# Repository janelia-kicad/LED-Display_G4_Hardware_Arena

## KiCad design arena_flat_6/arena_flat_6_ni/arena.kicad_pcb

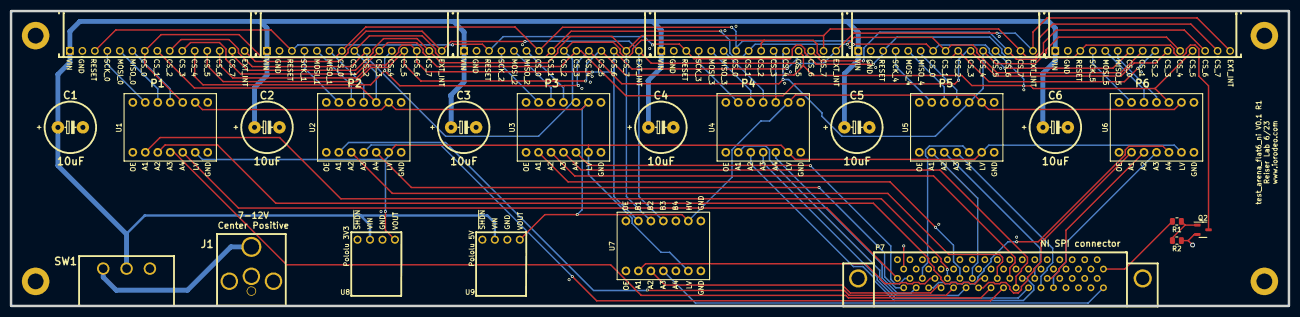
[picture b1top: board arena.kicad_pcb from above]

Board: 4 copper layers, 260.0 x 60.0 mm, 31 parts (0 on the bottom side), 62 nets.

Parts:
C1, C2, C3, C4, C5, C6: 10uF; Capacitor_Polarized
H1, H2, H3, H4: MountingHole_Pad; MountingHole_3.2mm_M3_DIN965_Pad
J1: Barrel_Jack; DCJACK_2PIN_HIGHCURRENT
P1, P2, P3, P4, P5, P6: CONN15; HEADER_TOP
P7: CONN_34X2; TE_CONN_DSUB_RA_68
Q2: MOSFET_NCHAN; SOT-23-3
R1: 200; R_0805_2012Metric
R2: 20k; R_0805_2012Metric
SW1: SW_SPDT; slide_switch
U1, U2, U3, U4, U5, U6, U7: VAL**; SPARKFUN_TXB0104
U8, U9: POLOLU_D24V6Fx; D24V6Fx

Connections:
/3V3: U1.6 (LV), U2.6 (LV), U3.6 (LV), U4.6 (LV), U5.6 (LV), U6.6 (LV), U7.6 (LV), U8.4 (VOUT)
/5V: U1.9 (HV), U2.9 (HV), U3.9 (HV), U4.9 (HV), U5.9 (HV), U6.9 (HV), U7.9 (HV), U9.4 (VOUT)
/CS_0_3V3: P7.35, U1.5 (A4)
/CS_0_5V: P1.7, P2.7, P3.7, P4.7, P5.7, P6.7, U1.10 (B4)
/CS_1_3V3: P7.36, U2.5 (A4)
/CS_1_5V: P1.8, P2.8, P3.8, P4.8, P5.8, P6.8, U2.10 (B4)
/CS_2_3V3: P7.37, U3.5 (A4)
/CS_2_5V: P1.9, P2.9, P3.9, P4.9, P5.9, P6.9, U3.10 (B4)
/CS_3_3V3: P7.38, U4.5 (A4)
/CS_3_5V: P1.10, P2.10, P3.10, P4.10, P5.10, P6.10, U4.10 (B4)
/CS_4_3V3: P7.39, U5.5 (A4)
/CS_4_5V: P1.11, P2.11, P3.11, P4.11, P5.11, P6.11, U5.10 (B4)
/CS_5_3V3: P7.40, U6.5 (A4)
/CS_5_5V: P1.12, P2.12, P3.12, P4.12, P5.12, P6.12, U6.10 (B4)
/CS_6_3V3: P7.41, U7.2 (A1)
/CS_6_5V: P1.13, P2.13, P3.13, P4.13, P5.13, P6.13, U7.13 (B1)
/CS_7_3V3: P7.42, U7.3 (A2)
/CS_7_5V: P1.14, P2.14, P3.14, P4.14, P5.14, P6.14, U7.12 (B2)
/EXT_INT_3V3: P7.68, U7.4 (A3)
/EXT_INT_5V: P1.15, P2.15, P3.15, P4.15, P5.15, P6.15, U7.11 (B3)
/MISO_0_3V3: P7.50, U1.4 (A3)
/MISO_0_5V: P1.6, U1.11 (B3)
/MISO_1_3V3: P7.52, U2.4 (A3)
/MISO_1_5V: P2.6, U2.11 (B3)
/MISO_2_3V3: P7.54, U3.4 (A3)
/MISO_2_5V: P3.6, U3.11 (B3)
/MISO_3_3V3: P7.56, U4.4 (A3)
/MISO_3_5V: P4.6, U4.11 (B3)
/MISO_4_3V3: P7.58, U5.4 (A3)
/MISO_4_5V: P5.6, U5.11 (B3)
/MISO_5_3V3: P7.60, U6.4 (A3)
/MISO_5_5V: P6.6, U6.11 (B3)
/MOSI_0_3V3: P7.49, U1.3 (A2)
/MOSI_0_5V: P1.5, U1.12 (B2)
/MOSI_1_3V3: P7.51, U2.3 (A2)
/MOSI_1_5V: P2.5, U2.12 (B2)
/MOSI_2_3V3: P7.53, U3.3 (A2)
/MOSI_2_5V: P3.5, U3.12 (B2)
/MOSI_3_3V3: P7.55, U4.3 (A2)
/MOSI_3_5V: P4.5, U4.12 (B2)
/MOSI_4_3V3: P7.57, U5.3 (A2)
/MOSI_4_5V: P5.5, U5.12 (B2)
/MOSI_5_3V3: P7.59, U6.3 (A2)
/MOSI_5_5V: P6.5, U6.12 (B2)
/RESET: P7.34, R1.2
/RESET_PAN: P1.3, P2.3, P3.3, P4.3, P5.3, P6.3, Q2.3 (D)
/SCK_0_3V3: P7.43, U1.2 (A1)
/SCK_0_5V: P1.4, U1.13 (B1)
/SCK_1_3V3: P7.44, U2.2 (A1)
/SCK_1_5V: P2.4, U2.13 (B1)
/SCK_2_3V3: P7.45, U3.2 (A1)
/SCK_2_5V: P3.4, U3.13 (B1)
/SCK_3_3V3: P7.46, U4.2 (A1)
/SCK_3_5V: P4.4, U4.13 (B1)
/SCK_4_3V3: P7.47, U5.2 (A1)
/SCK_4_5V: P5.4, U5.13 (B1)
/SCK_5_3V3: P7.48, U6.2 (A1)
/SCK_5_5V: P6.4, U6.13 (B1)
/VIN: C1.1, C2.1, C3.1, C4.1, C5.1, C6.1, P1.1, P2.1, P3.1, P4.1, P5.1, P6.1, SW1.2 (B), U8.2 (VIN), U9.2 (VIN)
/VIN_SW: J1.1, SW1.1 (A)
GND: C1.2, C2.2, C3.2, C4.2, C5.2, C6.2, H1.1, H2.1, H3.1, H4.1, J1.2, P1.2, P2.2, P3.2, P4.2, P5.2, P6.2, P7.1, P7.2, P7.3, P7.69, Q2.2 (S), R2.1, SW1.3 (C), U1.7 (GND), U1.8 (GND), U2.7 (GND), U2.8 (GND), U3.7 (GND), U3.8 (GND), U4.7 (GND), U4.8 (GND), U5.7 (GND), U5.8 (GND), U6.7 (GND), U6.8 (GND), U7.7 (GND), U7.8 (GND), U8.3 (GND), U9.3 (GND)
unnamed: Q2.1 (G), R1.1, R2.2

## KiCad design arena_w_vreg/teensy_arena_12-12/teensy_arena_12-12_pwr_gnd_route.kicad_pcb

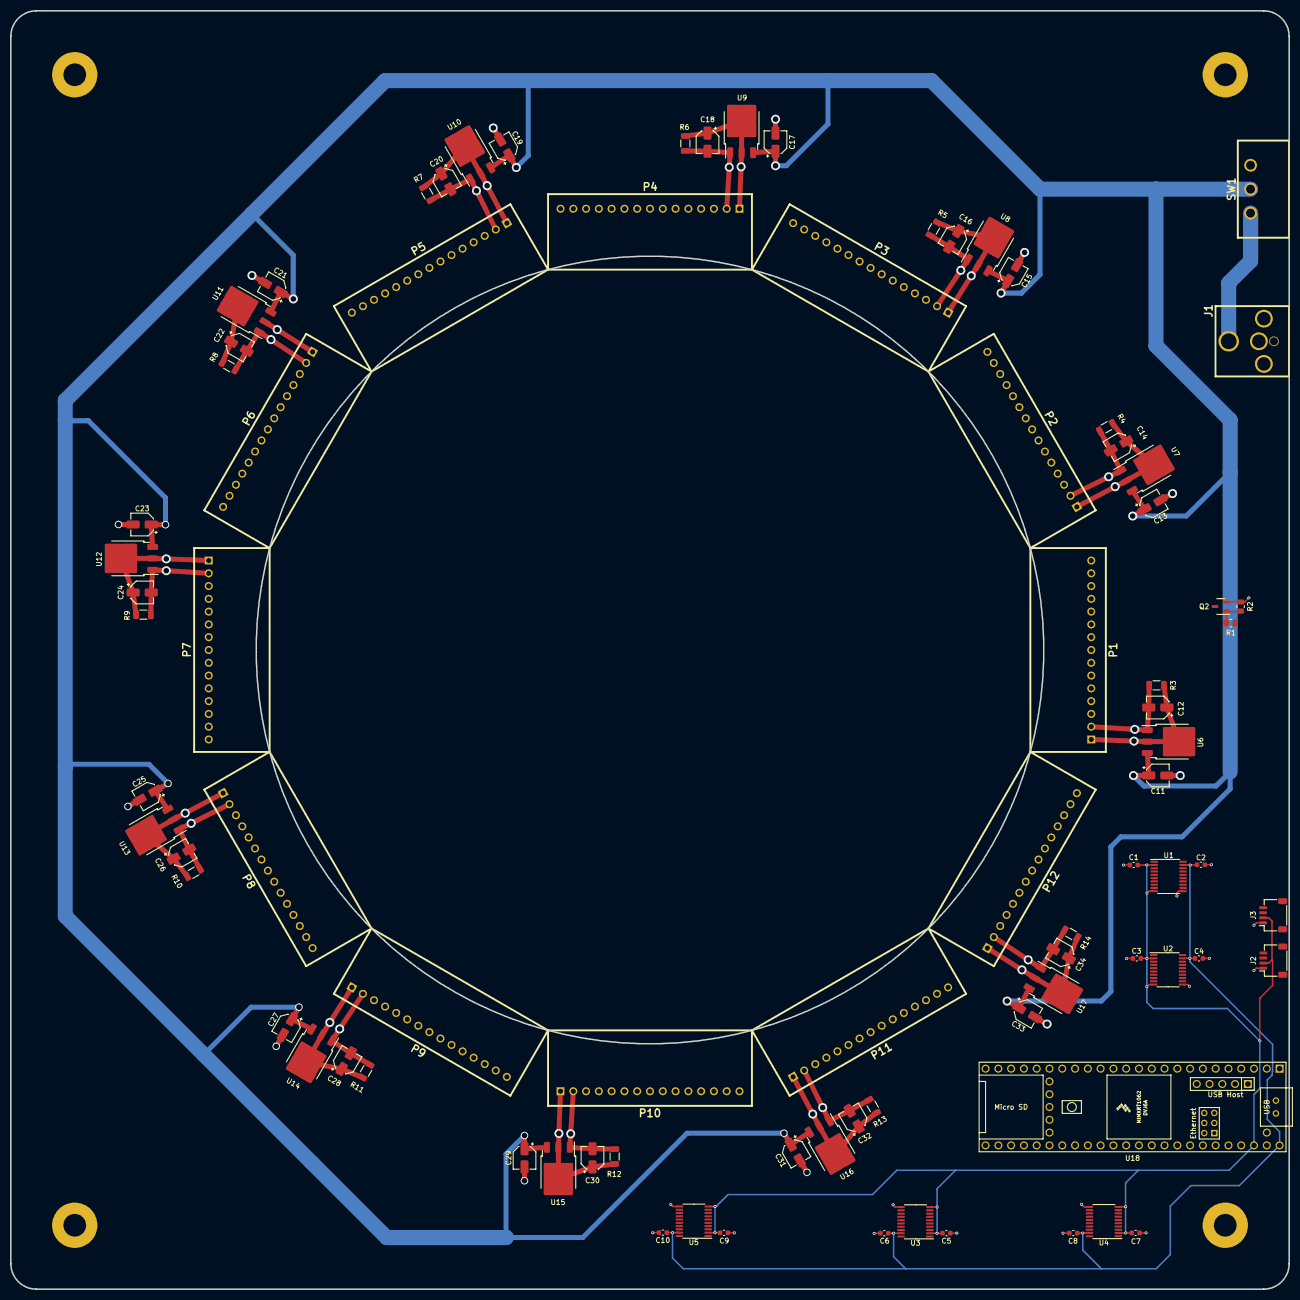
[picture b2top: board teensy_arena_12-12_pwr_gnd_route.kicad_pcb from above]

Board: 4 copper layers, 254.0 x 254.0 mm, 87 parts (0 on the bottom side), 98 nets.

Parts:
C1, C2, C3, C4, C5, C6, C7, C8, C9, C10: 0.1uF; C_0603_1608Metric
C11, C13, C15, C17, C21, C23, C25, C27, C29, C31, C33: 10uF; CP_Elec_4x5.4
C12, C14, C16, C18, C20, C22, C24, C26, C28, C30, C32, C34: 22uF; CP_Elec_4x5.4
C19: 10F; CP_Elec_4x5.4
H1, H2, H3, H4: MountingHole_Pad; MountingHole_4.5mm_Pad
J1: Barrel_Jack; DCJACK_2PIN_HIGHCURRENT
J2, J3: Conn_01x04; JST_SH_SM04B-SRSS-TB_1x04-1MP_P1.00mm_Horizontal
P1, P2, P3, P4, P5, P6, P7, P8, P9, P10, P11, P12: CONN15; HEADER_TOP
Q2: MOSFET_NCHAN; SOT-23-3
R1: 200; R_0805_2012Metric
R2: 20k; R_0805_2012Metric
R3, R4, R5, R6, R7, R8, R9, R10, R11, R12, R13, R14: 300; C_1206_3216Metric
SW1: SW_SPDT; slide_switch
U1, U2, U3, U4, U5: TXB0108PW; TSSOP-20_4.4x6.5mm_P0.65mm
U6, U7, U8, U9, U10, U11, U12, U13, U14, U15, U16, U17: AZ1084-5.0; TO-252-3_TabPin2
U18: Teensy4.1; Teensy41

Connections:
+3.3V: C1.1, C3.1, C5.1, C7.1, C9.1, J2.2, J3.2, U1.2 (VCCA), U1.10 (OE), U2.2 (VCCA), U2.10 (OE), U3.2 (VCCA), U3.10 (OE), U4.2 (VCCA), U4.10 (OE), U5.2 (VCCA), U5.10 (OE), U18.15 (3V3), U18.46 (3V3)
+5V: C2.1, C4.1, C6.1, C8.1, C10.1, U1.19 (VCCB), U2.19 (VCCB), U3.19 (VCCB), U4.19 (VCCB), U5.19 (VCCB), U18.48 (VIN), U18.49 (VUSB)
/Level Shifters/PAN3V.CS_00: U2.1 (A1), U18.2 (0_RX1_CRX2_CS1)
/Level Shifters/PAN3V.CS_01: U2.3 (A2), U18.4 (2_OUT2)
/Level Shifters/PAN3V.CS_02: U2.4 (A3), U18.5 (3_LRCLK2)
/Level Shifters/PAN3V.CS_03: U2.5 (A4), U18.6 (4_BCLK2)
/Level Shifters/PAN3V.CS_04: U2.6 (A5), U18.7 (5_IN2)
/Level Shifters/PAN3V.CS_05: U2.7 (A6), U18.8 (6_OUT1D)
/Level Shifters/PAN3V.CS_06: U2.8 (A7), U18.9 (7_RX2_OUT1A)
/Level Shifters/PAN3V.CS_07: U2.9 (A8), U18.10 (8_TX2_IN1)
/Level Shifters/PAN3V.CS_08: U3.1 (A1), U18.11 (9_OUT1C)
/Level Shifters/PAN3V.CS_09: U3.3 (A2), U18.12 (10_CS_MQSR)
/Level Shifters/PAN3V.CS_10: U3.4 (A3), U18.16 (24_A10_TX6_SCL2)
/Level Shifters/PAN3V.CS_11: U3.5 (A4), U18.17 (25_A11_RX6_SDA2)
/Level Shifters/PAN3V.CS_12: U3.6 (A5), U18.20 (28_RX7)
/Level Shifters/PAN3V.CS_13: U3.7 (A6), U18.21 (29_TX7)
/Level Shifters/PAN3V.CS_14: U3.8 (A7), U18.22 (30_CRX3)
/Level Shifters/PAN3V.CS_15: U3.9 (A8), U18.23 (31_CTX3)
/Level Shifters/PAN3V.CS_16: U4.1 (A1), U18.24 (32_OUT1B)
/Level Shifters/PAN3V.CS_17: U4.3 (A2), U18.45 (23_A9_CRX1_MCLK1)
/Level Shifters/PAN3V.CS_18: U4.4 (A3), U18.44 (22_A8_CTX1)
/Level Shifters/PAN3V.CS_19: U4.5 (A4), U18.43 (21_A7_RX5_BCLK1)
/Level Shifters/PAN3V.CS_20: U4.6 (A5), U18.42 (20_A6_TX5_LRCLK1)
/Level Shifters/PAN3V.CS_21: U4.7 (A6), U18.39 (17_A3_TX4_SDA1)
/Level Shifters/PAN3V.CS_22: U4.8 (A7), U18.38 (16_A2_RX4_SCL1)
/Level Shifters/PAN3V.CS_23: U4.9 (A8), U18.33 (41_A17)
/Level Shifters/PAN3V.CS_24: U5.1 (A1), U18.32 (40_A16)
/Level Shifters/PAN3V.CS_25: U5.3 (A2), U18.31 (39_MISO1_OUT1A)
/Level Shifters/PAN3V.CS_26: U5.4 (A3), U18.30 (38_CS1_IN1)
/Level Shifters/PAN3V.CS_27: U5.5 (A4), U18.29 (37_CS)
/Level Shifters/PAN3V.CS_28: U5.6 (A5), U18.28 (36_CS)
/Level Shifters/PAN3V.CS_29: U5.7 (A6), U18.27 (35_TX8)
/Level Shifters/PAN3V.EXT_INT: U5.9 (A8), U18.25 (33_MCLK2)
/Level Shifters/PAN3V.MISO_0: U1.5 (A4), U18.14 (12_MISO_MQSL)
/Level Shifters/PAN3V.MISO_1: U1.9 (A8), U18.3 (1_TX1_CTX2_MISO1)
/Level Shifters/PAN3V.MOSI_0: U1.4 (A3), U18.13 (11_MOSI_CTX1)
/Level Shifters/PAN3V.MOSI_1: U1.8 (A7), U18.18 (26_A12_MOSI1)
/Level Shifters/PAN3V.RESET: U1.1 (A1), U18.26 (34_RX8)
/Level Shifters/PAN3V.SCK_0: U1.3 (A2), U18.35 (13_SCK_LED)
/Level Shifters/PAN3V.SCK_1: U1.7 (A6), U18.19 (27_A13_SCK1)
/Level Shifters/PAN5V.CS_00: P1.7, P7.7, U2.20 (B1)
/Level Shifters/PAN5V.CS_01: P1.8, P7.8, U2.18 (B2)
/Level Shifters/PAN5V.CS_02: P1.9, P7.9, U2.17 (B3)
/Level Shifters/PAN5V.CS_03: P1.10, P7.10, U2.16 (B4)
/Level Shifters/PAN5V.CS_04: P1.11, P7.11, U2.15 (B5)
/Level Shifters/PAN5V.CS_05: P2.7, P8.7, U2.14 (B6)
/Level Shifters/PAN5V.CS_06: P2.8, P2.9, P8.8, P8.9, U2.13 (B7)
/Level Shifters/PAN5V.CS_08: P2.10, P8.10, U3.20 (B1)
/Level Shifters/PAN5V.CS_09: P2.11, P8.11, U3.18 (B2)
/Level Shifters/PAN5V.CS_10: P3.7, P9.7, U3.17 (B3)
/Level Shifters/PAN5V.CS_11: P3.8, P9.8, U3.16 (B4)
/Level Shifters/PAN5V.CS_12: P3.9, P9.9, U3.15 (B5)
/Level Shifters/PAN5V.CS_13: P3.10, P9.10, U3.14 (B6)
/Level Shifters/PAN5V.CS_14: P3.11, P9.11, U3.13 (B7)
/Level Shifters/PAN5V.CS_15: P4.7, P10.7, U3.12 (B8)
/Level Shifters/PAN5V.CS_16: P4.8, P10.8, U4.20 (B1)
/Level Shifters/PAN5V.CS_17: P4.9, P10.9, U4.18 (B2)
/Level Shifters/PAN5V.CS_18: P4.10, P10.10, U4.17 (B3)
/Level Shifters/PAN5V.CS_19: P4.11, P10.11, U4.16 (B4)
/Level Shifters/PAN5V.CS_20: P5.7, P11.7, U4.15 (B5)
/Level Shifters/PAN5V.CS_21: P5.8, P11.8, U4.14 (B6)
/Level Shifters/PAN5V.CS_22: P5.9, P11.9, U4.13 (B7)
/Level Shifters/PAN5V.CS_23: P5.10, P11.10, U4.12 (B8)
/Level Shifters/PAN5V.CS_24: P5.11, P11.11, U5.20 (B1)
/Level Shifters/PAN5V.CS_25: P6.7, P12.7, U5.18 (B2)
/Level Shifters/PAN5V.CS_26: P6.8, P12.8, U5.17 (B3)
/Level Shifters/PAN5V.CS_27: P6.9, P12.9, U5.16 (B4)
/Level Shifters/PAN5V.CS_28: P6.10, P12.10, U5.15 (B5)
/Level Shifters/PAN5V.CS_29: P6.11, P12.11, U5.14 (B6)
/Level Shifters/PAN5V.EXT_INT: P1.15, P2.15, P3.15, P4.15, P5.15, P6.15, P7.15, P8.15, P9.15, P10.15, P11.15, P12.15, U5.12 (B8)
/Level Shifters/PAN5V.MISO_0: P1.6, P2.6, P3.6, P4.6, P5.6, P6.6, U1.16 (B4)
/Level Shifters/PAN5V.MISO_1: P7.6, P8.6, P9.6, P10.6, P11.6, P12.6, U1.12 (B8)
/Level Shifters/PAN5V.MOSI_0: P1.5, P2.5, P3.5, P4.5, P5.5, P6.5, U1.17 (B3)
/Level Shifters/PAN5V.MOSI_1: P7.5, P8.5, P9.5, P10.5, P11.5, P12.5, U1.13 (B7)
/Level Shifters/PAN5V.RESET: R1.2, U1.20 (B1)
/Level Shifters/PAN5V.SCK_0: P1.4, P2.4, P3.4, P4.4, P5.4, P6.4, U1.18 (B2)
/Level Shifters/PAN5V.SCK_1: P7.4, P8.4, P9.4, P10.4, P11.4, P12.4, U1.14 (B6)
/Panel Headers/POW.5V_HDR_1: C12.1, P1.1, R3.1, U6.2 (VO)
/Panel Headers/POW.5V_HDR_2: C14.1, P2.1, R4.1, U7.2 (VO)
/Panel Headers/POW.5V_HDR_3: C16.1, P3.1, R5.1, U8.2 (VO)
/Panel Headers/POW.5V_HDR_4: C18.1, P4.1, R6.1, U9.2 (VO)
/Panel Headers/POW.5V_HDR_5: C20.1, P5.1, R7.1, U10.2 (VO)
/Panel Headers/POW.5V_HDR_6: C22.1, P6.1, R8.1, U11.2 (VO)
/Panel Headers/POW.5V_HDR_7: C24.1, P7.1, R9.1, U12.2 (VO)
/Panel Headers/POW.5V_HDR_8: C26.1, P8.1, R10.1, U13.2 (VO)
/Panel Headers/POW.5V_HDR_9: C28.1, P9.1, R11.1, U14.2 (VO)
/Panel Headers/POW.5V_HDR_10: C30.1, P10.1, R12.1, U15.2 (VO)
/Panel Headers/POW.5V_HDR_11: C32.1, P11.1, R13.1, U16.2 (VO)
/Panel Headers/POW.5V_HDR_12: C34.1, P12.1, R14.1, U17.2 (VO)
/Panel Headers/RESET: P1.3, P2.3, P3.3, P4.3, P5.3, P6.3, P7.3, P8.3, P9.3, P10.3, P11.3, P12.3, Q2.3 (D)
/Teensy/A0: J3.3, U18.36 (14_A0_TX3_SPDIF_OUT)
/Teensy/A1: J3.4, U18.37 (15_A1_RX3_SPDIF_IN)
/Teensy/SCL: J2.4, U18.41 (19_A5_SCL)
/Teensy/SDA: J2.3, U18.40 (18_A4_SDA)
GND: C1.2, C2.2, C3.2, C4.2, C5.2, C6.2, C7.2, C8.2, C9.2, C10.2, C11.2, C12.2, C13.2, C14.2, C15.2, C16.2, C17.2, C18.2, C19.2, C20.2, C21.2, C22.2, C23.2, C24.2, C25.2, C26.2, C27.2, C28.2, C29.2, C30.2, C31.2, C32.2, C33.2, C34.2, H1.1, H2.1, H3.1, H4.1, J1.2, J2.1, J3.1, P1.2, P2.2, P3.2, P4.2, P5.2, P6.2, P7.2, P8.2, P9.2, P10.2, P11.2, P12.2, Q2.2 (S), R2.1, R3.2, R4.2, R5.2, R6.2, R7.2, R8.2, R9.2, R10.2, R11.2, R12.2, R13.2, R14.2, SW1.3 (C), U1.11 (GND), U2.11 (GND), U3.11 (GND), U4.11 (GND), U5.11 (GND), U6.1 (GND), U7.1 (GND), U8.1 (GND), U9.1 (GND), U10.1 (GND), U11.1 (GND), U12.1 (GND), U13.1 (GND), U14.1 (GND), U15.1 (GND), U16.1 (GND), U17.1 (GND), U18.1 (GND), U18.34 (GND), U18.47 (GND)
unnamed: Q2.1 (G), R1.1, R2.2
unnamed: J1.1, SW1.1 (A)
VCC: C11.1, C13.1, C15.1, C17.1, C19.1, C21.1, C23.1, C25.1, C27.1, C29.1, C31.1, C33.1, SW1.2 (B), U6.3 (VI), U7.3 (VI), U8.3 (VI), U9.3 (VI), U10.3 (VI), U11.3 (VI), U12.3 (VI), U13.3 (VI), U14.3 (VI), U15.3 (VI), U16.3 (VI), U17.3 (VI)

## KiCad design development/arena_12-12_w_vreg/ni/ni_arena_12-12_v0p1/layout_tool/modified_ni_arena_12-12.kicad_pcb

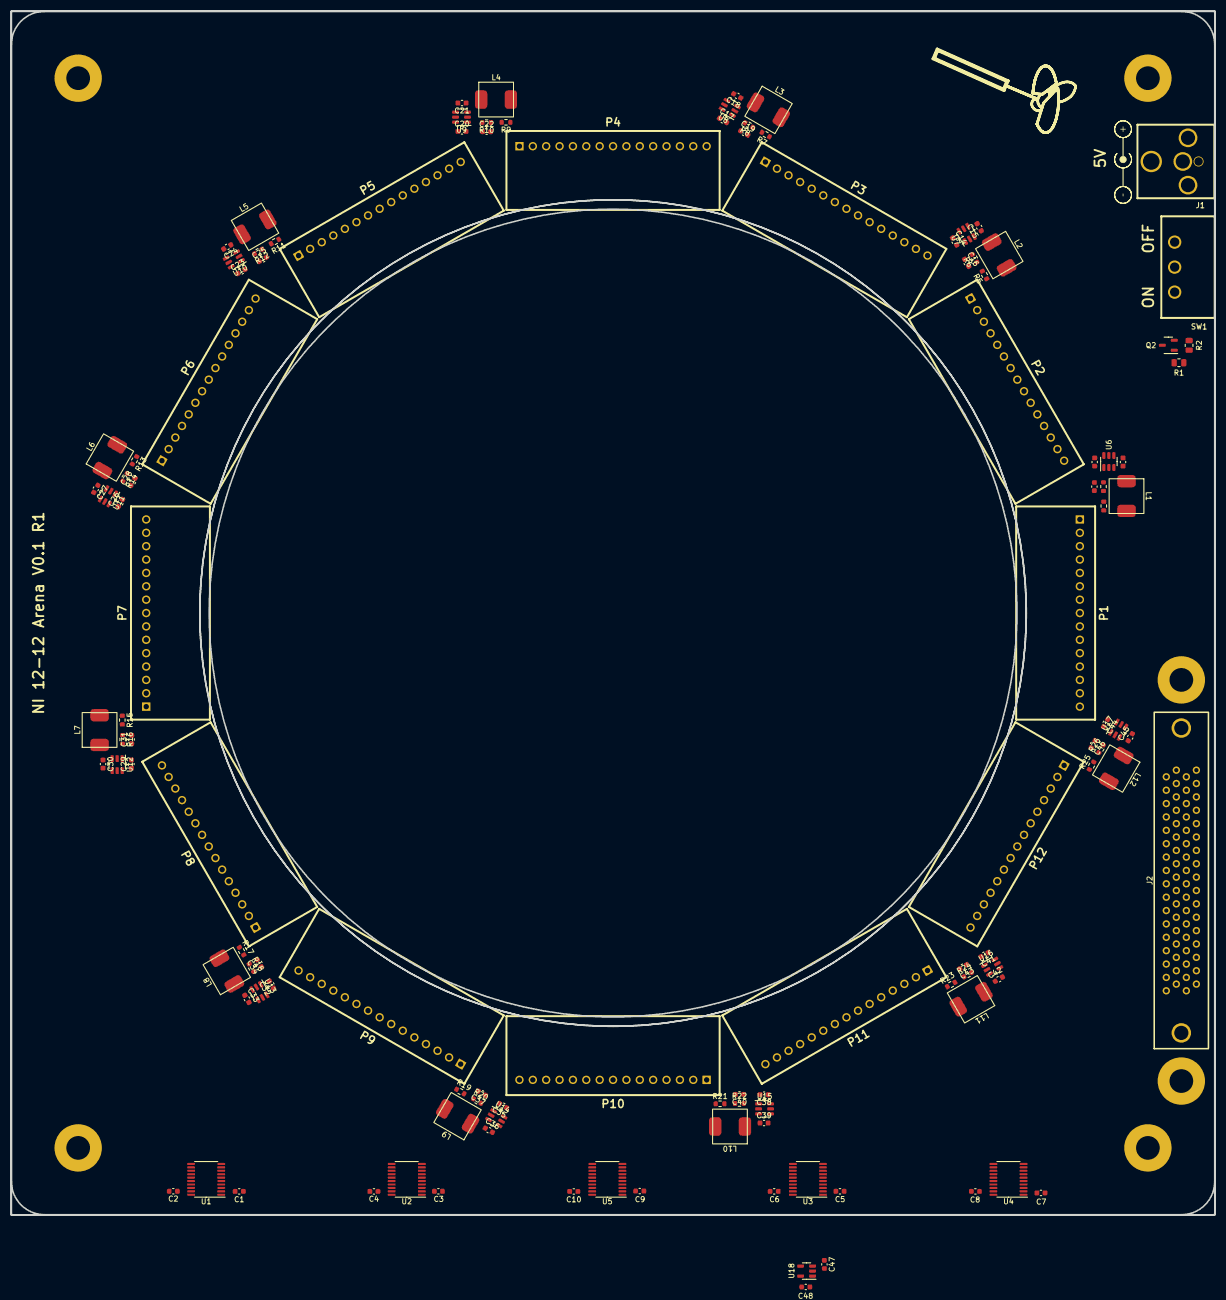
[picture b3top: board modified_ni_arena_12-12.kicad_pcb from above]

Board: 4 copper layers, 228.6 x 228.6 mm, 126 parts (0 on the bottom side), 134 nets, no tracks yet.

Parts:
C1, C2, C3, C4, C5, C6, C7, C8, C9, C10: 0.1uF; C_0603_1608Metric
C11, C15, C18, C21, C24, C27, C30, C33, C36, C39, C42, C45: 100nF; C_0603_1608Metric
C12, C14, C17, C20, C23, C26, C29, C32, C35, C38, C41, C44, C47, C48: 10uF; C_0603_1608Metric
C13, C16, C19, C22, C25, C28, C31, C34, C37, C40, C43, C46: 22uF; C_0603_1608Metric
H1, H2, H3, H4, H5, H6: MountingHole_Pad; MountingHole_4.5mm_Pad
J1: Barrel_Jack; DCJACK_2PIN_HIGHCURRENT
J2: NI_TE_68pos; TE_CONN_DSUB_VERT_68
L1, L2, L3, L4, L5, L6, L7, L8, L9, L10, L11, L12: 3.3uH; CYA0650_3P3UH
P1, P2, P3, P4, P5, P6, P7, P8, P9, P10, P11, P12: CONN15; HEADER_TOP
Q2: MOSFET_NCHAN; SOT-23-3
R1: 200; R_0805_2012Metric
R2: 20k; R_0805_2012Metric
R3, R5, R7, R9, R11, R13, R15, R17, R19, R21, R23, R25: 56.2k; R_0603_1608Metric
R4, R6, R8, R10, R12, R14, R16, R18, R20, R22, R24, R26: 10k; R_0603_1608Metric
SW1: SW_SPDT; slide_switch
U1, U2, U3, U4, U5: TXB0108PW; TSSOP-20_4.4x6.5mm_P0.65mm
U6, U7, U8, U9, U10, U11, U12, U13, U14, U15, U16, U17: TPS564201DDC; SOT-23-6
U18: AP2112K-3.3; SOT-23-5

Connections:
+3.3V: C1.1, C3.1, C5.1, C7.1, C9.1, C48.1, U1.2 (VCCA), U1.10 (OE), U2.2 (VCCA), U2.10 (OE), U3.2 (VCCA), U3.10 (OE), U4.2 (VCCA), U4.10 (OE), U5.2 (VCCA), U5.10 (OE), U18.5 (VOUT)
/Level Shifters/PAN3V.CS_00: J2.68, U1.1 (A1)
/Level Shifters/PAN3V.CS_01: J2.67, U1.3 (A2)
/Level Shifters/PAN3V.CS_02: J2.66, U1.4 (A3)
/Level Shifters/PAN3V.CS_03: J2.65, U1.5 (A4)
/Level Shifters/PAN3V.CS_04: J2.64, U1.6 (A5)
/Level Shifters/PAN3V.CS_05: J2.63, U1.7 (A6)
/Level Shifters/PAN3V.CS_06: J2.62, U1.8 (A7)
/Level Shifters/PAN3V.CS_07: J2.61, U1.9 (A8)
/Level Shifters/PAN3V.EXT_INT: J2.35, U5.8 (A7)
/Level Shifters/PAN3V.MISO_00: J2.53, U2.9 (A8)
/Level Shifters/PAN3V.MISO_01: J2.51, U3.3 (A2)
/Level Shifters/PAN3V.MISO_02: J2.49, U3.5 (A4)
/Level Shifters/PAN3V.MISO_03: J2.47, U3.7 (A6)
/Level Shifters/PAN3V.MISO_04: J2.45, U3.9 (A8)
/Level Shifters/PAN3V.MISO_05: J2.43, U4.3 (A2)
/Level Shifters/PAN3V.MISO_06: J2.41, U4.5 (A4)
/Level Shifters/PAN3V.MISO_07: J2.40, U4.7 (A6)
/Level Shifters/PAN3V.MISO_08: J2.39, U4.9 (A8)
/Level Shifters/PAN3V.MISO_09: J2.38, U5.3 (A2)
/Level Shifters/PAN3V.MISO_10: J2.37, U5.5 (A4)
/Level Shifters/PAN3V.MISO_11: J2.36, U5.7 (A6)
/Level Shifters/PAN3V.MOSI_00: J2.54, U2.8 (A7)
/Level Shifters/PAN3V.MOSI_01: J2.52, U3.1 (A1)
/Level Shifters/PAN3V.MOSI_02: J2.50, U3.4 (A3)
/Level Shifters/PAN3V.MOSI_03: J2.48, U3.6 (A5)
/Level Shifters/PAN3V.MOSI_04: J2.46, U3.8 (A7)
/Level Shifters/PAN3V.MOSI_05: J2.44, U4.1 (A1)
/Level Shifters/PAN3V.MOSI_06: J2.42, U4.4 (A3)
/Level Shifters/PAN3V.MOSI_07: J2.29, U4.6 (A5)
/Level Shifters/PAN3V.MOSI_08: J2.30, U4.8 (A7)
/Level Shifters/PAN3V.MOSI_09: J2.31, U5.1 (A1)
/Level Shifters/PAN3V.MOSI_10: J2.32, U5.4 (A3)
/Level Shifters/PAN3V.MOSI_11: J2.33, U5.6 (A5)
/Level Shifters/PAN3V.RESET: J2.34, U5.9 (A8)
/Level Shifters/PAN3V.SCK_00: J2.60, U2.1 (A1)
/Level Shifters/PAN3V.SCK_01: J2.59, U2.3 (A2)
/Level Shifters/PAN3V.SCK_02: J2.58, U2.4 (A3)
/Level Shifters/PAN3V.SCK_03: J2.57, U2.5 (A4)
/Level Shifters/PAN3V.SCK_04: J2.56, U2.6 (A5)
/Level Shifters/PAN3V.SCK_05: J2.55, U2.7 (A6)
/Level Shifters/PAN5V.CS_00: P1.7, P2.7, P3.7, P4.7, P5.7, P6.7, P7.7, P8.7, P9.7, P10.7, P11.7, P12.7, U1.20 (B1)
/Level Shifters/PAN5V.CS_01: P1.8, P2.8, P3.8, P4.8, P5.8, P6.8, P7.8, P8.8, P9.8, P10.8, P11.8, P12.8, U1.18 (B2)
/Level Shifters/PAN5V.CS_02: P1.9, P2.9, P3.9, P4.9, P5.9, P6.9, P7.9, P8.9, P9.9, P10.9, P11.9, P12.9, U1.17 (B3)
/Level Shifters/PAN5V.CS_03: P1.10, P2.10, P3.10, P4.10, P5.10, P6.10, P7.10, P8.10, P9.10, P10.10, P11.10, P12.10, U1.16 (B4)
/Level Shifters/PAN5V.CS_04: P1.11, P2.11, P3.11, P4.11, P5.11, P6.11, P7.11, P8.11, P9.11, P10.11, P11.11, P12.11, U1.15 (B5)
/Level Shifters/PAN5V.CS_05: P1.12, P2.12, P3.12, P4.12, P5.12, P6.12, P7.12, P8.12, P9.12, P10.12, P11.12, P12.12, U1.14 (B6)
/Level Shifters/PAN5V.CS_06: P1.13, P2.13, P3.13, P4.13, P5.13, P6.13, P7.13, P8.13, P9.13, P10.13, P11.13, P12.13, U1.13 (B7)
/Level Shifters/PAN5V.CS_07: P1.14, P2.14, P3.14, P4.14, P5.14, P6.14, P7.14, P8.14, P9.14, P10.14, P11.14, P12.14, U1.12 (B8)
/Level Shifters/PAN5V.EXT_INT: P1.15, P2.15, P3.15, P4.15, P5.15, P6.15, P7.15, P8.15, P9.15, P10.15, P11.15, P12.15, U5.13 (B7)
/Level Shifters/PAN5V.MISO_00: P1.6, U2.12 (B8)
/Level Shifters/PAN5V.MISO_01: P2.6, U3.18 (B2)
/Level Shifters/PAN5V.MISO_02: P3.6, U3.16 (B4)
/Level Shifters/PAN5V.MISO_03: P4.6, U3.14 (B6)
/Level Shifters/PAN5V.MISO_04: P5.6, U3.12 (B8)
/Level Shifters/PAN5V.MISO_05: P6.6, U4.18 (B2)
/Level Shifters/PAN5V.MISO_06: P7.6, U4.16 (B4)
/Level Shifters/PAN5V.MISO_07: P8.6, U4.14 (B6)
/Level Shifters/PAN5V.MISO_08: P9.6, U4.12 (B8)
/Level Shifters/PAN5V.MISO_09: P10.6, U5.18 (B2)
/Level Shifters/PAN5V.MISO_10: P11.6, U5.16 (B4)
/Level Shifters/PAN5V.MISO_11: P12.6, U5.14 (B6)
/Level Shifters/PAN5V.MOSI_00: P1.5, U2.13 (B7)
/Level Shifters/PAN5V.MOSI_01: P2.5, U3.20 (B1)
/Level Shifters/PAN5V.MOSI_02: P3.5, U3.17 (B3)
/Level Shifters/PAN5V.MOSI_03: P4.5, U3.15 (B5)
/Level Shifters/PAN5V.MOSI_04: P5.5, U3.13 (B7)
/Level Shifters/PAN5V.MOSI_05: P6.5, U4.20 (B1)
/Level Shifters/PAN5V.MOSI_06: P7.5, U4.17 (B3)
/Level Shifters/PAN5V.MOSI_07: P8.5, U4.15 (B5)
/Level Shifters/PAN5V.MOSI_08: P9.5, U4.13 (B7)
/Level Shifters/PAN5V.MOSI_09: P10.5, U5.20 (B1)
/Level Shifters/PAN5V.MOSI_10: P11.5, U5.17 (B3)
/Level Shifters/PAN5V.MOSI_11: P12.5, U5.15 (B5)
/Level Shifters/PAN5V.RESET: R1.2, U5.12 (B8)
/Level Shifters/PAN5V.SCK_00: P1.4, P7.4, U2.20 (B1)
/Level Shifters/PAN5V.SCK_01: P2.4, P8.4, U2.18 (B2)
/Level Shifters/PAN5V.SCK_02: P3.4, P9.4, U2.17 (B3)
/Level Shifters/PAN5V.SCK_03: P4.4, P10.4, U2.16 (B4)
/Level Shifters/PAN5V.SCK_04: P5.4, P11.4, U2.15 (B5)
/Level Shifters/PAN5V.SCK_05: P6.4, P12.4, U2.14 (B6)
/Level Shifters/POW.5V_HDR_1: C13.2, C47.1, L1.2, P1.1, R3.1, U18.1 (VIN), U18.3 (EN)
/Level Shifters/POW.5V_HDR_2: C16.2, L2.2, P2.1, R5.1
/Level Shifters/POW.5V_HDR_3: C19.2, L3.2, P3.1, R7.1
/Level Shifters/POW.5V_HDR_4: C22.2, L4.2, P4.1, R9.1
/Level Shifters/POW.5V_HDR_5: C25.2, L5.2, P5.1, R11.1
/Level Shifters/POW.5V_HDR_6: C28.2, L6.2, P6.1, R13.1
/Level Shifters/POW.5V_HDR_7: C31.2, L7.2, P7.1, R15.1
/Level Shifters/POW.5V_HDR_8: C34.2, L8.2, P8.1, R17.1
/Level Shifters/POW.5V_HDR_9: C37.2, L9.2, P9.1, R19.1
/Level Shifters/POW.5V_HDR_10: C2.1, C4.1, C6.1, C8.1, C10.1, C40.2, L10.2, P10.1, R21.1, U1.19 (VCCB), U2.19 (VCCB), U3.19 (VCCB), U4.19 (VCCB), U5.19 (VCCB)
/Level Shifters/POW.5V_HDR_11: C43.2, L11.2, P11.1, R23.1
/Level Shifters/POW.5V_HDR_12: C46.2, L12.2, P12.1, R25.1
/Panel Headers/RESET: P1.3, P2.3, P3.3, P4.3, P5.3, P6.3, P7.3, P8.3, P9.3, P10.3, P11.3, P12.3, Q2.3 (D)
GND: C1.2, C2.2, C3.2, C4.2, C5.2, C6.2, C7.2, C8.2, C9.2, C10.2, C12.2, C13.1, C14.2, C16.1, C17.2, C19.1, C20.2, C22.1, C23.2, C25.1, C26.2, C28.1, C29.2, C31.1, C32.2, C34.1, C35.2, C37.1, C38.2, C40.1, C41.2, C43.1, C44.2, C46.1, C47.2, C48.2, H1.1, H2.1, H3.1, H4.1, H5.1, H6.1, J1.2, J2.1, J2.2, J2.3, J2.69 (GND), J2.70 (GND), P1.2, P2.2, P3.2, P4.2, P5.2, P6.2, P7.2, P8.2, P9.2, P10.2, P11.2, P12.2, Q2.2 (S), R2.1, R4.2, R6.2, R8.2, R10.2, R12.2, R14.2, R16.2, R18.2, R20.2, R22.2, R24.2, R26.2, SW1.3 (C), U1.11 (GND), U2.11 (GND), U3.11 (GND), U4.11 (GND), U5.11 (GND), U6.1 (GND), U7.1 (GND), U8.1 (GND), U9.1 (GND), U10.1 (GND), U11.1 (GND), U12.1 (GND), U13.1 (GND), U14.1 (GND), U15.1 (GND), U16.1 (GND), U17.1 (GND), U18.2 (GND)
unnamed: Q2.1 (G), R1.1, R2.2
unnamed: J1.1, SW1.1 (A)
unnamed: C11.2, L1.1, U6.2 (SW)
unnamed: C11.1, U6.6 (VBST)
unnamed: R3.2, R4.1, U6.4 (VFB)
unnamed: C15.2, L2.1, U7.2 (SW)
unnamed: C15.1, U7.6 (VBST)
unnamed: R5.2, R6.1, U7.4 (VFB)
unnamed: C18.2, L3.1, U8.2 (SW)
unnamed: C18.1, U8.6 (VBST)
unnamed: R7.2, R8.1, U8.4 (VFB)
unnamed: C21.2, L4.1, U9.2 (SW)
unnamed: C21.1, U9.6 (VBST)
unnamed: R9.2, R10.1, U9.4 (VFB)
unnamed: C24.2, L5.1, U10.2 (SW)
unnamed: C24.1, U10.6 (VBST)
unnamed: R11.2, R12.1, U10.4 (VFB)
unnamed: C27.2, L6.1, U11.2 (SW)
unnamed: C27.1, U11.6 (VBST)
unnamed: R13.2, R14.1, U11.4 (VFB)
unnamed: C30.2, L7.1, U12.2 (SW)
unnamed: C30.1, U12.6 (VBST)
unnamed: R15.2, R16.1, U12.4 (VFB)
unnamed: C33.2, L8.1, U13.2 (SW)
unnamed: C33.1, U13.6 (VBST)
unnamed: R17.2, R18.1, U13.4 (VFB)
unnamed: C36.2, L9.1, U14.2 (SW)
unnamed: C36.1, U14.6 (VBST)
unnamed: R19.2, R20.1, U14.4 (VFB)
unnamed: C39.2, L10.1, U15.2 (SW)
unnamed: C39.1, U15.6 (VBST)
unnamed: R21.2, R22.1, U15.4 (VFB)
unnamed: C42.2, L11.1, U16.2 (SW)
unnamed: C42.1, U16.6 (VBST)
unnamed: R23.2, R24.1, U16.4 (VFB)
unnamed: C45.2, L12.1, U17.2 (SW)
unnamed: C45.1, U17.6 (VBST)
unnamed: R25.2, R26.1, U17.4 (VFB)
VCC: C12.1, C14.1, C17.1, C20.1, C23.1, C26.1, C29.1, C32.1, C35.1, C38.1, C41.1, C44.1, SW1.2 (B), U6.3 (VIN), U6.5 (EN), U7.3 (VIN), U7.5 (EN), U8.3 (VIN), U8.5 (EN), U9.3 (VIN), U9.5 (EN), U10.3 (VIN), U10.5 (EN), U11.3 (VIN), U11.5 (EN), U12.3 (VIN), U12.5 (EN), U13.3 (VIN), U13.5 (EN), U14.3 (VIN), U14.5 (EN), U15.3 (VIN), U15.5 (EN), U16.3 (VIN), U16.5 (EN), U17.3 (VIN), U17.5 (EN)

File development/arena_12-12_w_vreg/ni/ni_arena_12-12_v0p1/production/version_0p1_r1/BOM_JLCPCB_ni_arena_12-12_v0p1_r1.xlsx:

Comment | Designator | Footprint | LCSC Part #（optional） | Qty
0.1uF ceramic Capacitor | C1, C2, C3, C4, C5, C6, C7, C8, C9, C10 | 0603 | C1591 | 10
10uF Ceramic Capacitor | C11, C14, C17, C20, C23, C26, C29, C32, C35, C38, C41, C44, C47, C48 | 0603 |  | 14
100nF Ceramic Capacitor | C12, C15, C18, C21, C24, C27, C30, C33, C36, C39, C42, C45 | 0603 |  | 12
22uF Ceramic Capacitor | C13, C16, C19, C22, C25, C28, C31, C34, C37, C40, C43, C46 | 0603 |  | 12
3.3uH Inductor | L1, L2, L3, L4, L5, L6, L7, L8, L9, L10, L11, L12 |  | C5189747 | 12
200 Ohm resistor | R1 | 0805 | C17540 | 1
20k Ohms resistor | R2 | 0805 | C4328 | 1
56.2k Resistor | R3, R5, R7, R9, R11, R13, R15, R17, R19, R21, R23, R25 | 0603 |  | 12
10k Resistor | R4, R6, R8, R10, R12, R14, R16, R18, R20, R22, R24, R26 | 0603 |  | 12
MOSFET N-channel | Q2 | SOT-23 | C165220 | 1
Level shifter TXB0108PWR | U1,U2,U3,U4,U5 | TSSOP-20 | C53406 | 5
TPS564201DDC Step-Down Regulator | U6, U7, U8, U9, U10, U11, U12, U13, U14, U15, U16, U17 | TSOT-23-6 | C464812 | 12
AP2112K-3.3 3.3V Linear Regulator | U18 | SOT-25-5 | C51118 | 1
DC Power Barrel Jack | J1 | through hole | global parts | 1
TE/NI 68 Position Connector | J2 | through hole | global parts | 1
15x1 female header, 0.1in pitch | P1,P2,P3,P4,P5,P6,P7,P8,P9,P10,P11,P12 | through hole | global parts | 12
Slide Switch SPDT | SW1 | through hole | global parts | 1
